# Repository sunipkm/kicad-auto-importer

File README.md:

# kicad-auto-importer

<!---->

A Rust workspace with two companion desktop applications for KiCad,
built on a shared, GUI-agnostic core library — each has its own README
with full details:

- **[`kicad-auto-importer`](crates/app/README.md)** — watches a folder
  for part-provider ZIP downloads (UltraLibrarian / Mouser / DigiKey)
  and imports the symbol / footprint / 3-D model files straight into a
  KiCad project's libraries. This is the original application the
  repository is named after.
- **[`kicad-bom`](kicad-bom/README.md)** — a standalone Tauri app for
  populating a schematic's bill of materials with manufacturer/
  distributor data and generating a priced, multi-vendor PDF/XLSX BOM
  report.

The two apps each keep their own Mouser/DigiKey API credentials and
settings (separate `settings.json` files), but share the KiCad
source-file primitives (S-expression parsing, `.kicad_sym`/`.kicad_sch`
handling, project/library-table resolution) from `crates/core` — see
[Workspace layout](#workspace-layout) below.

## Workspace layout

- `crates/core` — core KiCad source-file primitives shared by both
  apps: sexp (S-expression) parsing and writing, `.kicad_sym` symbol-
  library and `.kicad_sch` schematic parsing/patching, and
  `sym-lib-table`/`fp-lib-table`/project-file resolution. No GUI
  dependency, no app-specific business logic — fully unit tested on its
  own.
- `crates/app` — the egui-based GUI, and this app's own exclusive
  logic: the symbol/footprint/3-D-model import pipeline, the folder-
  watcher's settle/debounce logic, and its project-scoped config
  persistence — plus the main window (watch folder, symbol/footprint
  library paths, options, a start/stop toggle, and an activity log),
  the Import-From-Another-Project sub-window, and system tray
  integration. See [`crates/app/README.md`](crates/app/README.md).
- `kicad-bom` — a standalone Tauri (Rust backend + React/TypeScript
  frontend) app for Populate BOM and Generate BOM — see
  [`kicad-bom/README.md`](kicad-bom/README.md). Split out of `crates/app`
  because a richer, multi-vendor result picker needed more UI
  flexibility than egui's table widgets comfortably give; its backend
  owns its own Mouser/DigiKey lookup, BOM grouping/pricing, and
  PDF/XLSX report generation logic (`parts_lookup`/`bom_pricing`/
  `bom_report`/`populate_bom`/`generate_bom` modules), reusing only
  `crates/core`'s schematic/symbol-library primitives.

## Development

`test-project/` is a fixture KiCad project used to manually smoke-test
both apps (watcher/import, Populate/Generate BOM). Running the apps
against it can leave it locally modified, so its tracked files are kept
under `git update-index --skip-worktree` — Git ignores those local
edits by default. To intentionally update the fixture:

```sh
./scripts/test-project.sh unlock   # allow edits/staging/commits
# ...edit, git add, git commit...
./scripts/test-project.sh lock     # re-protect
```

Run `./scripts/test-project.sh reset` to discard local edits and
restore the committed content (re-locks automatically), or `status` to
see the current lock state.

## License

MIT — see [LICENSE](LICENSE).

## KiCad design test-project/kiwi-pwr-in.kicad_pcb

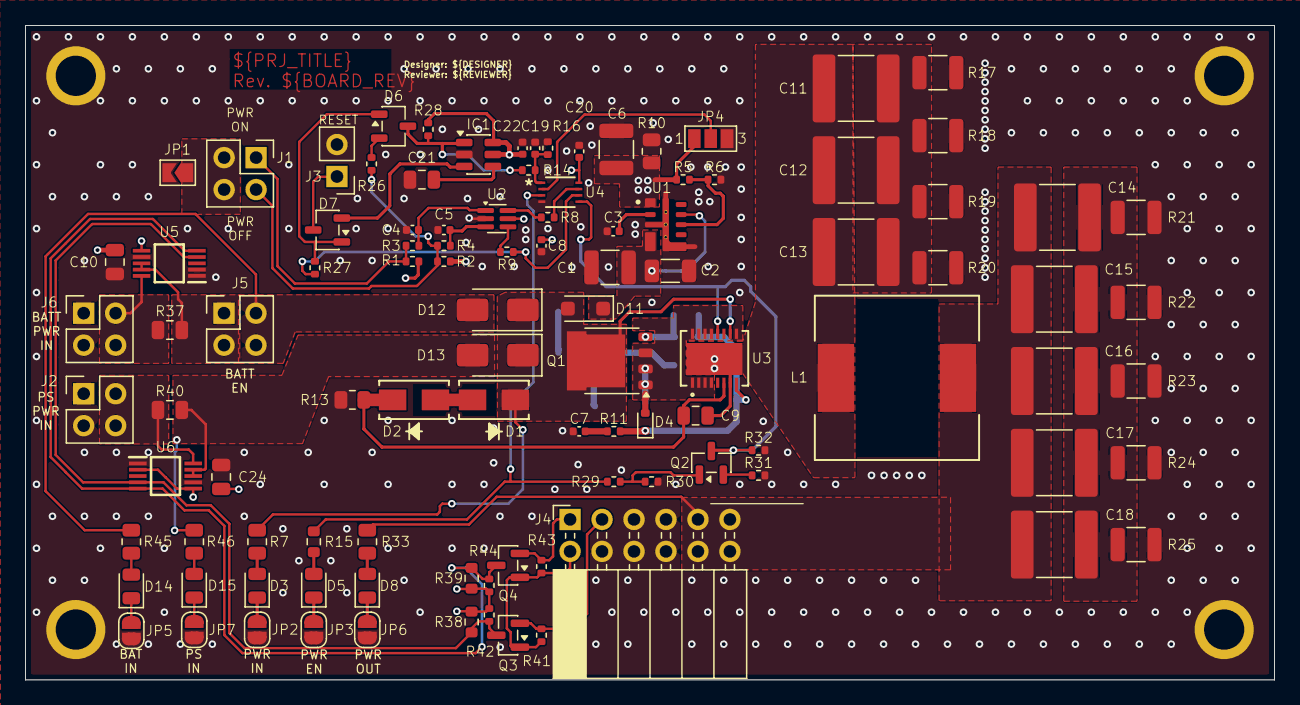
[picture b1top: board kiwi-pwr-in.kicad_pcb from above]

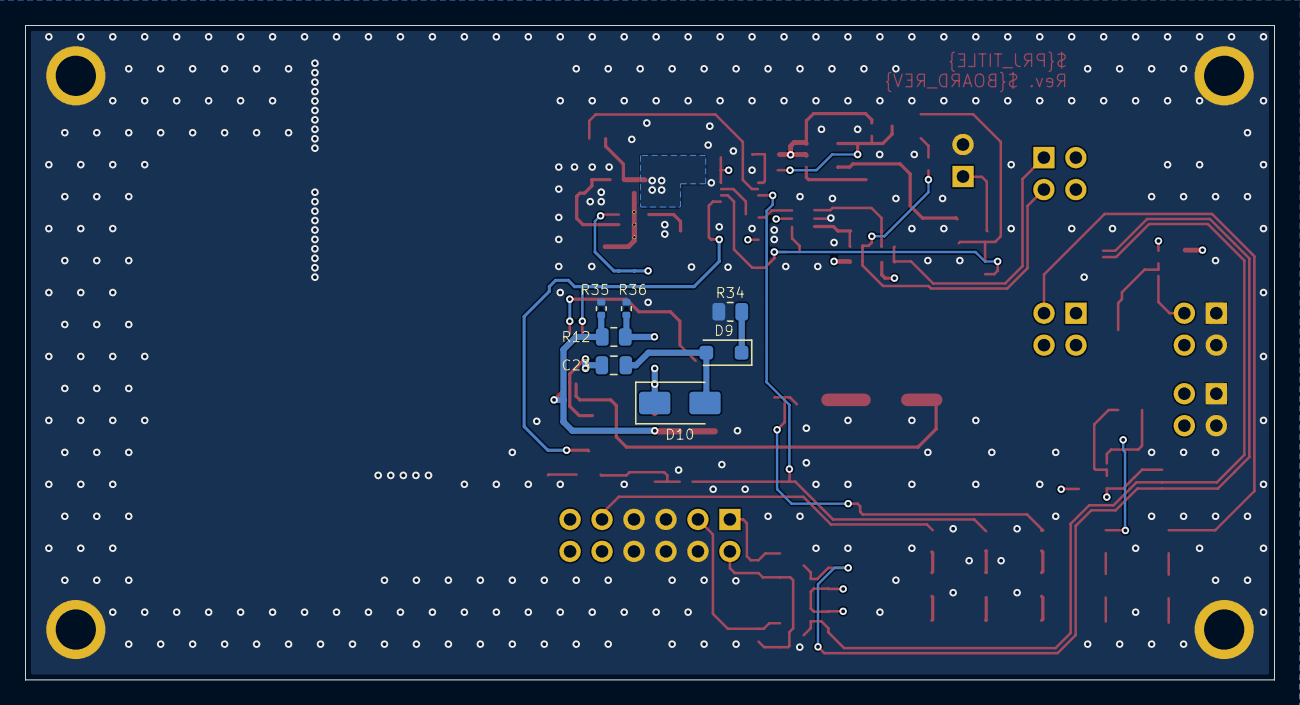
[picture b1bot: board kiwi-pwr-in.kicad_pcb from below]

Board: 4 copper layers, 99.2 x 52.0 mm, 114 parts (7 on the bottom side), 59 nets.

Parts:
C1: 10u; C_1210_3225Metric
C2: 2.2u; C_1206_3216Metric
C3, C4, C5, C8, C20, C22: 0.1u; C_0402_1005Metric
C6: 22u; C_1210_3225Metric
C7: 0.01u; C_0402_1005Metric
C9: 1.5u; C_0805_2012Metric
C10, C24: 0.1u; C_0805_2012Metric
C11, C12, C13, C14, C15, C16, C17, C18: 15u; C_2220_5750Metric
C19: 1u; C_0402_1005Metric
C21, C23: 0.47u; C_0805_2012Metric
D1: SMAJ40A; SMASeries_LTF
D2: SMAJ24A; SMASeries_LTF
D3, D8, D14, D15: GREEN; LED_0805_2012Metric
D4: DDZ9699T; D_SOD-523
D5: RED; LED_0805_2012Metric
D6, D7: BAT54C; SOT-23-3
D9, D11: 1N4148W; D_SOD-123F
D10: ES1B; D_SMA
D12, D13: TSSA5U60H; D_SMA
H1, H2, H3, H4: MountingHole_Pad; MountingHole_2.7mm_M2.5_DIN965_Pad
IC1: TPS3808G50QDBVRQ1; SOT-23-6
J1: PS_ON_OFF; PinHeader_2x02_P2.54mm_Vertical
J2: PS In; PinHeader_2x02_P2.54mm_Vertical
J3: Master_Reset; PinHeader_1x02_P2.54mm_Vertical
J4: OUTPUT; PinSocket_2x06_P2.54mm_Horizontal
J5: BATT_PLUG; PinHeader_2x02_P2.54mm_Vertical
J6: BATT In; PinHeader_2x02_P2.54mm_Vertical
JP1: Jumper_2_Bridged; SolderJumper-2_P1.3mm_Open_TrianglePad1.0x1.5mm
JP2, JP3, JP6: POWLED; SolderJumper-2_P1.3mm_Open_RoundedPad1.0x1.5mm
JP4: DOR_TIE; SolderJumper-3_P1.3mm_Open_Pad1.0x1.5mm_NumberLabels
JP5: BATLED; SolderJumper-2_P1.3mm_Open_RoundedPad1.0x1.5mm
JP7: PSLED; SolderJumper-2_P1.3mm_Open_RoundedPad1.0x1.5mm
L1: 2.2uh; IND_BOURNS_SRR1260
Q1: BUK7J2R4; LFPAK56
Q2, Q3, Q4: BSS138; SOT-23
R1, R2, R16, R30: 100k; R_0402_1005Metric
R3, R4: 100; R_0402_1005Metric
R5: 0; R_0402_1005Metric
R6: 32.4k; R_0402_1005Metric
R7, R33, R45, R46: 5.6k; R_0805_2012Metric
R8, R9, R11, R14, R26, R27, R29, R32, R35, R36, R41, R42, R43, R44: 10k; R_0402_1005Metric
R10, R13, R34: 1k; R_0805_2012Metric
R12: 10; R_0805_2012Metric
R15: 402; R_0603_1608Metric
R17, R18, R19, R20, R21, R22, R23, R24, R25: 0.27; R_1210_3225Metric
R28: 50k; R_0402_1005Metric
R31: 1k; R_0402_1005Metric
R37, R40: 20m; C_0805_2012Metric
R38, R39: 10k; R_0603_1608Metric
U1: TPSM265R1V5SILR; CONV_TPSM265R1V5SILR
U2: 74LVC2G17GW-Q100H; SOT-363_SC-70-6
U3: LTC4376HDHD-TRPBF; 05-08-1707_ADI
U4: 74LVC1G74DC-Q100H; DCU8-L
U5, U6: INA233AIDGSR; SOP50P490X110-10N

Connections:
+3V3_PI: J4.2, Q3.1 (G), Q4.1 (G), R41.2, R43.2
+5V: C6.2, C8.1, C10.1, C20.1, C22.1, C24.1, IC1.5 (SENSE), IC1.6 (VDD), JP4.1 (A), R1.2, R2.2, R5.2, R10.1, R28.1, R38.1, R39.1, R42.2, R44.2, U1.1 (VOUT), U2.5 (VCC), U4.8 (VCC), U5.6 (VS), U6.2 (A0), U6.6 (VS)
+28V: C14.1, C15.1, C16.1, C17.1, C18.1, J4.9, J4.10, J4.11, J4.12, L1.2, R33.1
+BATT: J5.1, J5.3, R37.2, U5.8 (Vbus), U5.9 (Vin-)
+PBATT: D12.2 (A), J5.2, J5.4, R45.1
+PS: J2.2, J2.4, R40.1, U6.10 (Vin+)
+PS_SEN: D13.2 (A), R40.2, R46.1, U6.8 (Vbus), U6.9 (Vin-)
+PWR: D1.1 (A1), D11.2 (A), D12.1 (K), D13.1 (K), Q1.5 (D), R7.1, U3.10 (INK)
+VBATT: J6.2, J6.4, R37.1, U5.10 (Vin+)
-BATT: C1.1, C2.1, C3.2, C4.2, C5.2, C6.1, C7.2, C8.2, C10.2, C19.2, C20.2, C21.2, C22.2, C24.2, H1.1 (1_1), H2.1 (1_1), H3.1 (1_1), H4.1 (1_1), IC1.2 (GND), J2.1, J2.3, J3.2, J4.4, J4.5, J4.6, J4.7, J4.8, J6.1, J6.3, JP1.2 (B), JP2.1 (A), JP3.1 (A), JP4.3 (B), JP5.1 (A), JP6.1 (A), JP7.1 (A), R6.1, R10.2, R13.2, R16.2, R17.2, R18.2, R19.2, R20.2, R21.2, R22.2, R23.2, R24.2, R25.2, R30.1, R31.1, R32.1, R34.2, R35.1, R36.1, U1.3_6_11 (GND), U1.12 (GND), U1.13 (GND), U1.14 (GND), U2.2 (GND), U4.4 (GND), U5.1 (A1), U5.2 (A0), U5.7 (GND), U6.1 (A1), U6.7 (GND)
/CIP_RTN: J1.3, J1.4, JP1.1 (A)
/DOR_CLEAR: R9.2, R27.1, U4.6 (~CLR)
/DOR_D: JP4.2 (C), U4.2 (D)
/DOR_PRE: R8.2, U4.7 (~PRE)
/DOR_SHDN: Q2.3 (D), R32.2, U3.12 (~SHDN), U4.5 (Q)
/DOR_~RESET: D6.3, IC1.1 (~RESET), R14.1, R28.2
/GND_ISO: C14.2, C15.2, C16.2, C17.2, C18.2, R21.1, R22.1, R23.1, R24.1, R25.1
/GND_ISO2: C11.2, C12.2, C13.2, R17.1, R18.1, R19.1, R20.1
/IN_ID: D4.2 (A), D10.1 (K), Q1.1 (S), Q1.2 (S), Q1.3 (S), U3.1 (IN), U3.2 (IN), U3.3 (IN), U3.4 (IN), U3.9 (CS), U3.13 (IN), U3.14 (IN), U3.15 (IN), U3.16 (IN)
/OUT_ID: C9.1, C11.1, C12.1, C13.1, C23.2, L1.1, U3.7 (OUTK), U3.17 (OUT)
/SCL_3V3: J4.1, Q4.2 (S), R43.1
/SCL_5V: Q4.3 (D), R39.2, R44.1, U5.5 (SCL), U6.5 (SCL)
/SDA_3V3: J4.3, Q3.2 (S), R41.1
/SDA_5V: Q3.3 (D), R38.2, R42.1, U5.4 (SDA), U6.4 (SDA)
/SHDN_GATE: R15.2, R29.1, U4.3 (~Q)
/VSS: C9.2, D2.1 (A1), R13.1, U3.6 (VSS)
/~DOR_OFF: J1.2, R2.1, R4.2, R26.1
/~DOR_ON: J1.1, R1.1, R3.2
unnamed: C4.1, R3.1, U2.1
unnamed: C5.1, R4.1, U2.3
unnamed: C7.1, R11.1
unnamed: D1.2 (A2), D2.2 (A2)
unnamed: D3.2 (A), R7.2
unnamed: D3.1 (K), JP2.2 (B)
unnamed: D4.1 (K), R11.2, R12.2, R35.2, U3.8 (GATE)
unnamed: D5.2 (A), R15.1
unnamed: D5.1 (K), JP3.2 (B)
unnamed: D6.1, D7.1, R27.2
unnamed: D6.2, R26.2
unnamed: D8.2 (A), R33.2
unnamed: D8.1 (K), JP6.2 (B)
unnamed: D9.1 (K), R34.1
unnamed: C23.1, D9.2 (A), D10.2 (A)
unnamed: C1.2, C2.2, D11.1 (K), U1.4_5 (VIN), U1.9 (EN)
unnamed: D14.2 (A), R45.2
unnamed: D14.1 (K), JP5.2 (B)
unnamed: D15.2 (A), R46.2
unnamed: D15.1 (K), JP7.2 (B)
unnamed: C21.1, IC1.4 (CT)
unnamed: D7.2, IC1.3 (~MR)
unnamed: D7.3, J3.1
unnamed: Q1.4 (G), R12.1, R36.2
unnamed: Q2.1 (G), R29.2, R30.2
unnamed: Q2.2 (S), R31.2
unnamed: R8.1, U2.6
unnamed: R9.1, U2.4
unnamed: R5.1, R6.2, U1.8 (SENSE+/FB)
unnamed: C3.1, U1.2 (SS)
unnamed: C19.1, R14.2, R16.1, U4.1 (CLK)
